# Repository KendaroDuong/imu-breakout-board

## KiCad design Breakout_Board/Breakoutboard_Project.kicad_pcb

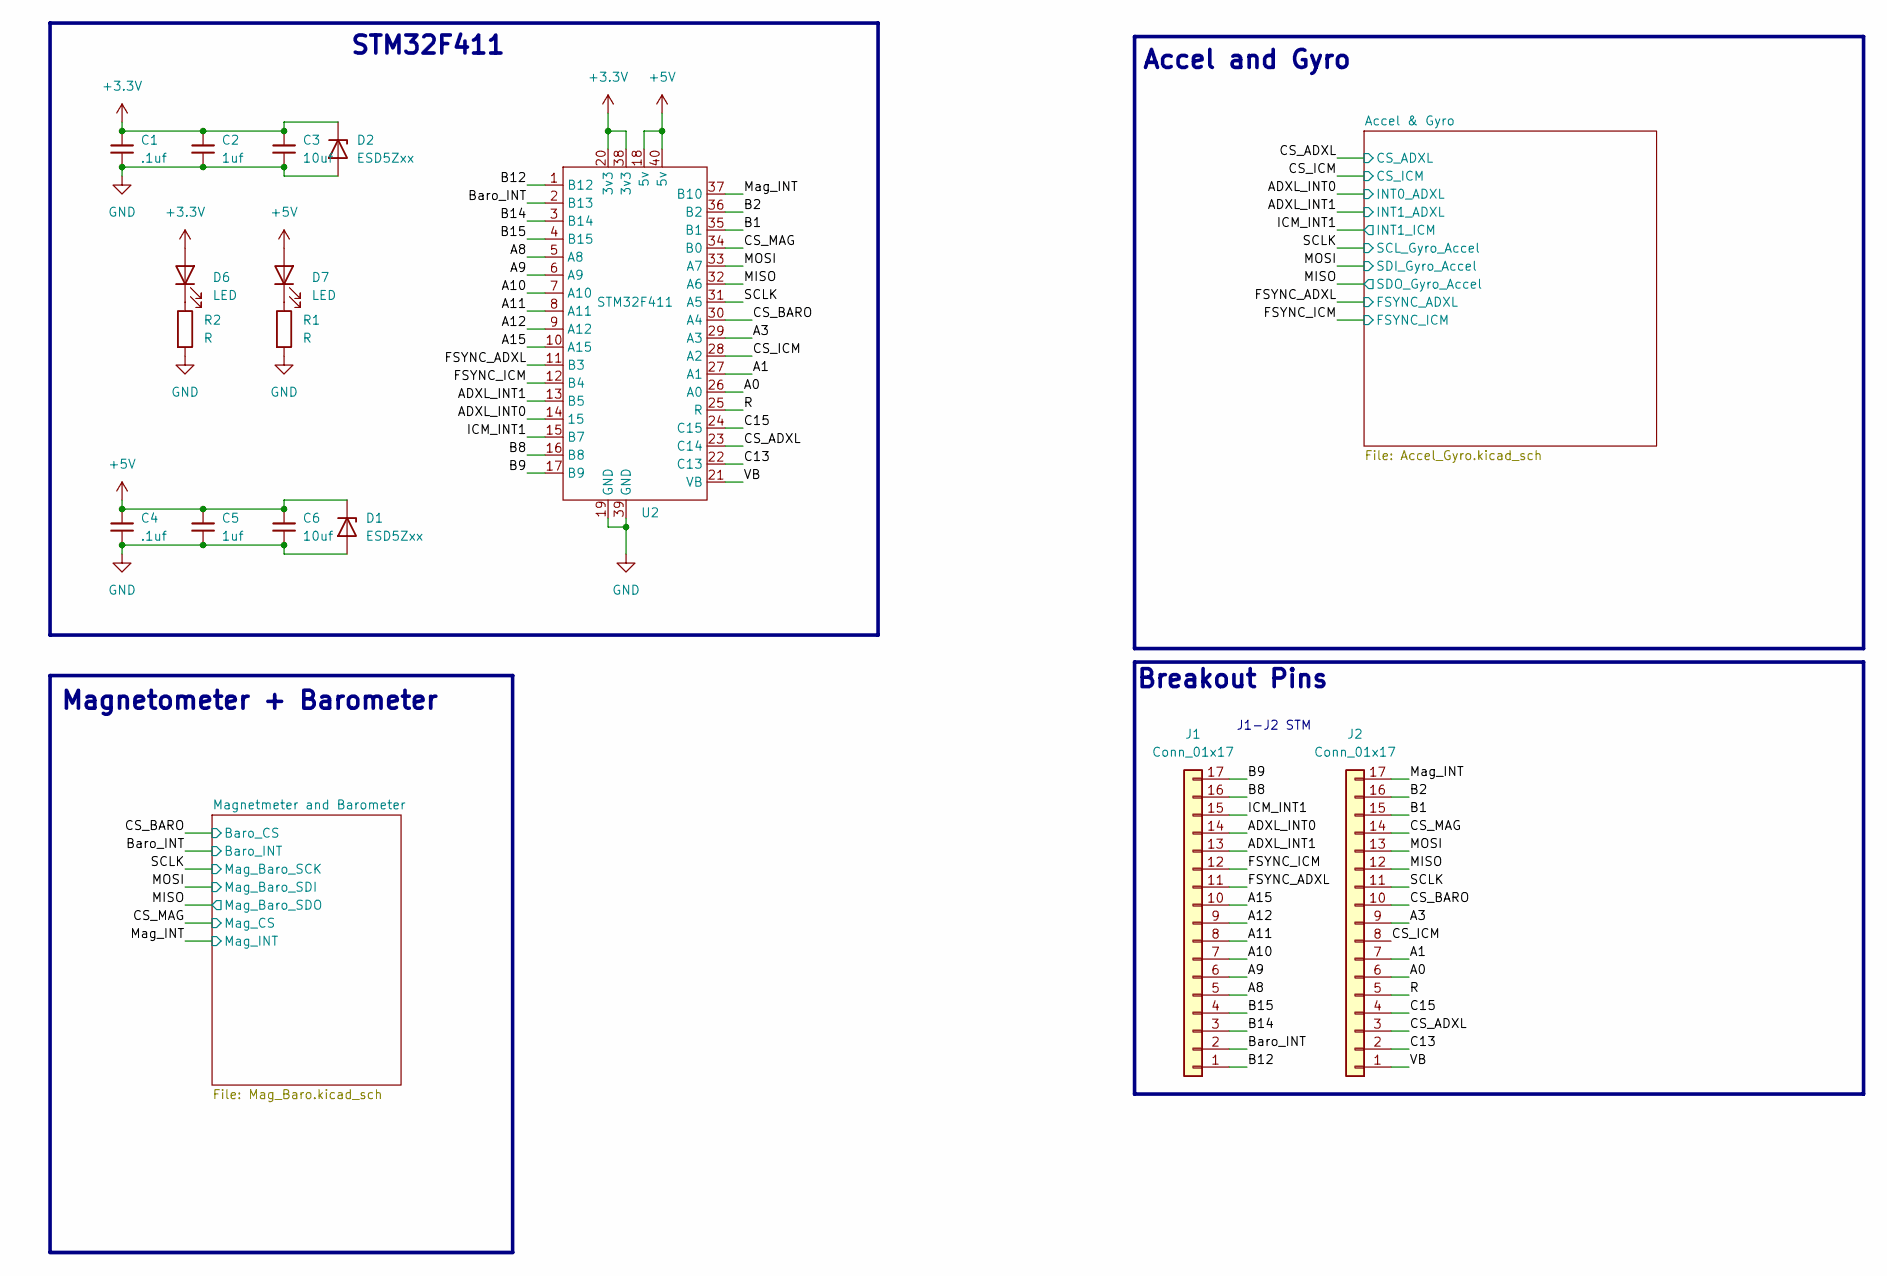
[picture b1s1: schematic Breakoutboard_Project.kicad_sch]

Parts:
C1, C4: .1uf; C_0805_2012Metric_Pad1.18x1.45mm_HandSolder
C2, C5: 1uf; C_0805_2012Metric_Pad1.18x1.45mm_HandSolder
C3, C6: 10uf; C_0805_2012Metric_Pad1.18x1.45mm_HandSolder
D1, D2: ESD5Zxx; D_SOD-523
D6, D7: LED; LED_0805_2012Metric_Pad1.15x1.40mm_HandSolder
J1, J2: Conn_01x17; PinHeader_1x17_P2.54mm_Vertical
R1, R2: R; LED_0805_2012Metric_Pad1.15x1.40mm_HandSolder
U2: STM32F411; BlackpillGeneric

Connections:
+3.3V: C1.1, C2.1, C3.1, D2.1 (K), D6.2 (A), U2.20 (3v3), U2.38 (3v3); also elsewhere on the board
+5V: C4.1, C5.1, C6.1, D1.1 (K), D7.2 (A), U2.18 (5v), U2.40 (5v)
/A0: J2.6, U2.26 (A0)
/A1: J2.7, U2.27 (A1)
/A3: J2.9, U2.29 (A3)
/A8: J1.5, U2.5 (A8)
/A9: J1.6, U2.6 (A9)
/A10: J1.7, U2.7 (A10)
/A11: J1.8, U2.8 (A11)
/A12: J1.9, U2.9 (A12)
/A15: J1.10, U2.10 (A15)
/ADXL_INT0: J1.14, U2.14 (15); also elsewhere on the board
/ADXL_INT1: J1.13, U2.13 (B5); also elsewhere on the board
/B1: J2.15, U2.35 (B1)
/B2: J2.16, U2.36 (B2)
/B8: J1.16, U2.16 (B8)
/B9: J1.17, U2.17 (B9)
/B12: J1.1, U2.1 (B12)
/B14: J1.3, U2.3 (B14)
/B15: J1.4, U2.4 (B15)
/Baro_INT: J1.2, U2.2 (B13); also elsewhere on the board
/C13: J2.2, U2.22 (C13)
/C15: J2.4, U2.24 (C15)
/CS_ADXL: J2.3, U2.23 (C14); also elsewhere on the board
/CS_BARO: J2.10, U2.30 (A4); also elsewhere on the board
/CS_ICM: J2.8, U2.28 (A2); also elsewhere on the board
/CS_MAG: J2.14, U2.34 (B0); also elsewhere on the board
/FSYNC_ADXL: J1.11, U2.11 (B3); also elsewhere on the board
/FSYNC_ICM: J1.12, U2.12 (B4); also elsewhere on the board
/ICM_INT1: J1.15, U2.15 (B7); also elsewhere on the board
/MISO: J2.12, U2.32 (A6); also elsewhere on the board
/MOSI: J2.13, U2.33 (A7); also elsewhere on the board
/Mag_INT: J2.17, U2.37 (B10); also elsewhere on the board
/R: J2.5, U2.25 (R)
/SCLK: J2.11, U2.31 (A5); also elsewhere on the board
/VB: J2.1, U2.21 (VB)
GND: C1.2, C2.2, C3.2, C4.2, C5.2, C6.2, D1.2 (A), D2.2 (A), R1.2, R2.2, U2.19 (GND), U2.39 (GND); also elsewhere on the board
unnamed: D6.1 (K), R2.1
unnamed: D7.1 (K), R1.1

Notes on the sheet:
Breakout Pins
STM32F411
Magnetometer + Barometer
Accel and Gyro
J1-J2 STM

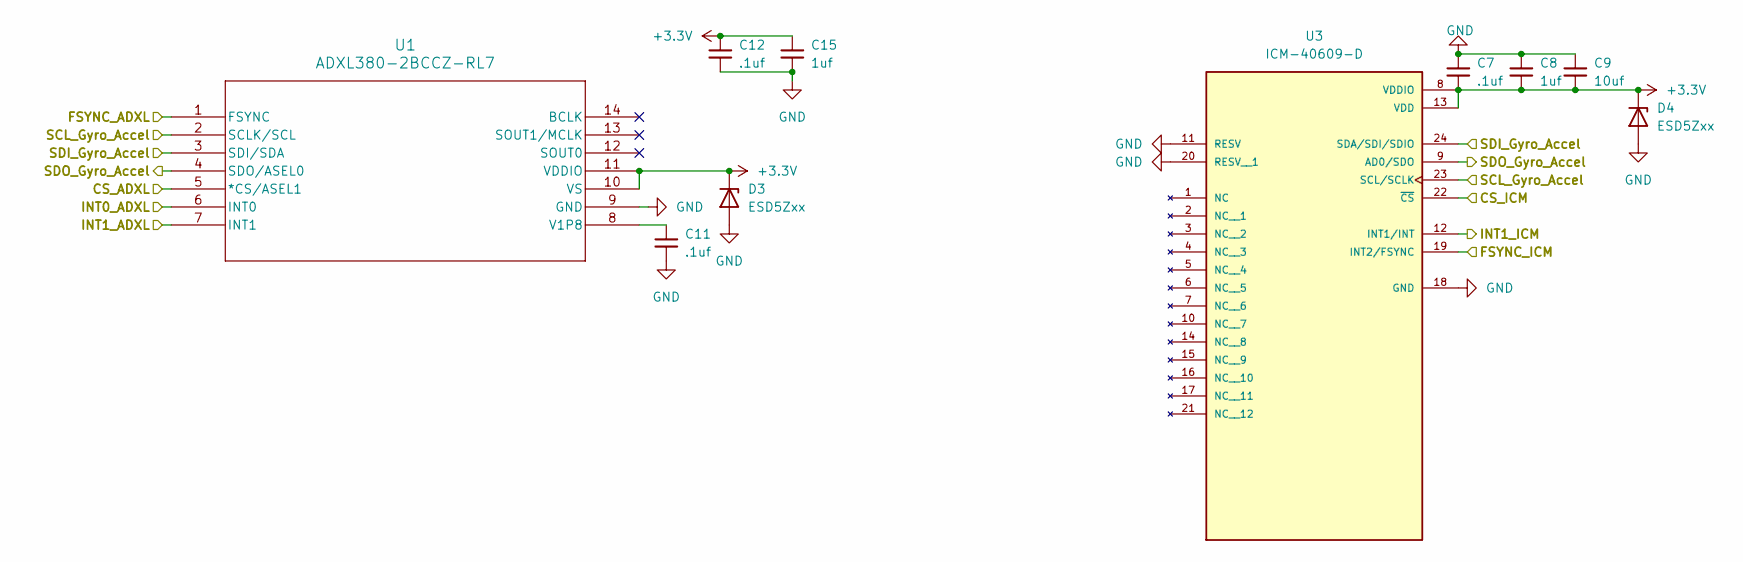
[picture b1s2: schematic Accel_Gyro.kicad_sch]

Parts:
C7, C11, C12: .1uf; C_0805_2012Metric_Pad1.18x1.45mm_HandSolder
C8, C15: 1uf; C_0805_2012Metric_Pad1.18x1.45mm_HandSolder
C9: 10uf; C_0805_2012Metric_Pad1.18x1.45mm_HandSolder
D3, D4: ESD5Zxx; D_SOD-523
U1: ADXL380-2BCCZ-RL7; CC-14-3_ADI
U3: ICM-40609-D; XDCR_ICM-40609-D; PARTREV 1.2

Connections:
+3.3V: C7.2, C8.2, C9.2, C12.1, C15.1, D3.1 (K), D4.1 (K), U1.10 (VS), U1.11 (VDDIO), U3.8 (VDDIO), U3.13 (VDD); also elsewhere on the board
/ADXL_INT0: U1.6 (INT0); also elsewhere on the board
/ADXL_INT1: U1.7 (INT1); also elsewhere on the board
/CS_ADXL: U1.5 (*CS/ASEL1); also elsewhere on the board
/CS_ICM: U3.22 (~CS); also elsewhere on the board
/FSYNC_ADXL: U1.1 (FSYNC); also elsewhere on the board
/FSYNC_ICM: U3.19 (INT2/FSYNC); also elsewhere on the board
/ICM_INT1: U3.12 (INT1/INT); also elsewhere on the board
/MISO: U1.4 (SDO/ASEL0), U3.9 (AD0/SDO); also elsewhere on the board
/MOSI: U1.3 (SDI/SDA), U3.24 (SDA/SDI/SDIO); also elsewhere on the board
/SCLK: U1.2 (SCLK/SCL), U3.23 (SCL/SCLK); also elsewhere on the board
GND: C7.1, C8.1, C9.1, C11.2, C12.2, C15.2, D3.2 (A), D4.2 (A), U1.9 (GND), U3.11 (RESV), U3.18 (GND), U3.20 (RESV__1); also elsewhere on the board
unnamed: C11.1, U1.8 (V1P8)

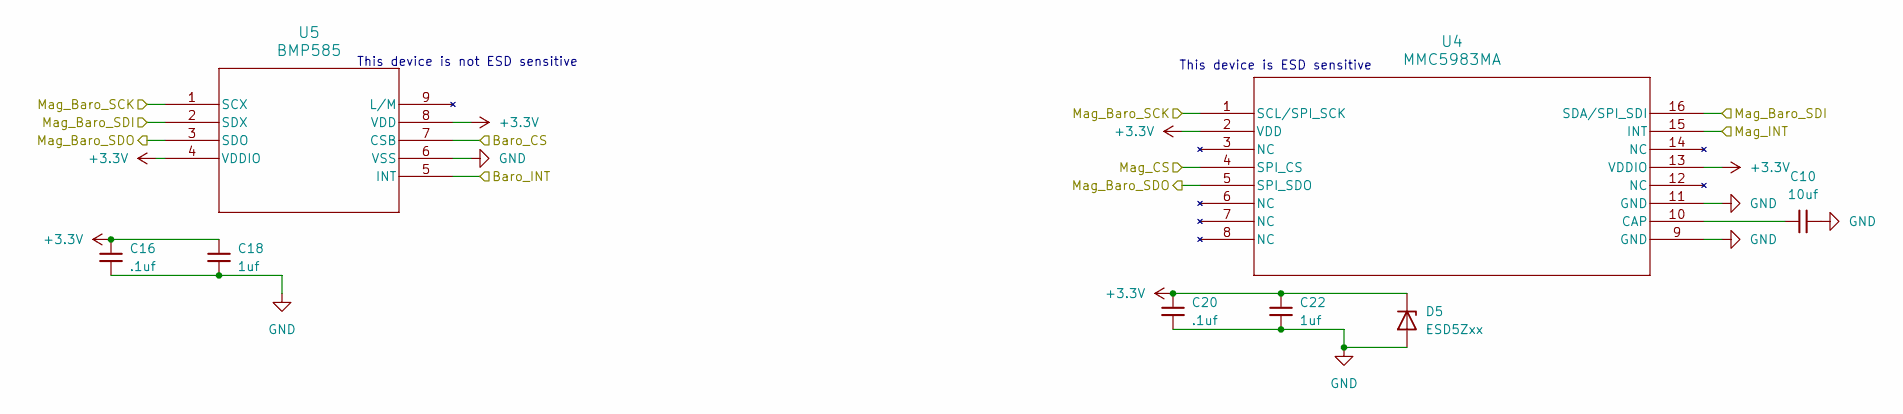
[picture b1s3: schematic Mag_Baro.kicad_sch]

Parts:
C10: 10uf; C_0805_2012Metric_Pad1.18x1.45mm_HandSolder
C16, C20: .1uf; C_0805_2012Metric_Pad1.18x1.45mm_HandSolder
C18, C22: 1uf; C_0805_2012Metric_Pad1.18x1.45mm_HandSolder
D5: ESD5Zxx; D_SOD-523
U4: MMC5983MA; MMC5983MA_MEM
U5: BMP585; LGA9_BMP585_BOS

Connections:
+3.3V: C16.1, C18.1, C20.1, C22.1, D5.1 (K), U4.2 (VDD), U4.13 (VDDIO), U5.4 (VDDIO), U5.8 (VDD); also elsewhere on the board
/Baro_INT: U5.5 (INT); also elsewhere on the board
/CS_BARO: U5.7 (CSB); also elsewhere on the board
/CS_MAG: U4.4 (SPI_CS); also elsewhere on the board
/MISO: U4.5 (SPI_SDO), U5.3 (SDO); also elsewhere on the board
/MOSI: U4.16 (SDA/SPI_SDI), U5.2 (SDX); also elsewhere on the board
/Mag_INT: U4.15 (INT); also elsewhere on the board
/SCLK: U4.1 (SCL/SPI_SCK), U5.1 (SCX); also elsewhere on the board
GND: C10.2, C16.2, C18.2, C20.2, C22.2, D5.2 (A), U4.9 (GND), U4.11 (GND), U5.6 (VSS); also elsewhere on the board
unnamed: C10.1, U4.10 (CAP)

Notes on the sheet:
This device is not ESD sensitive
This device is ESD sensitive

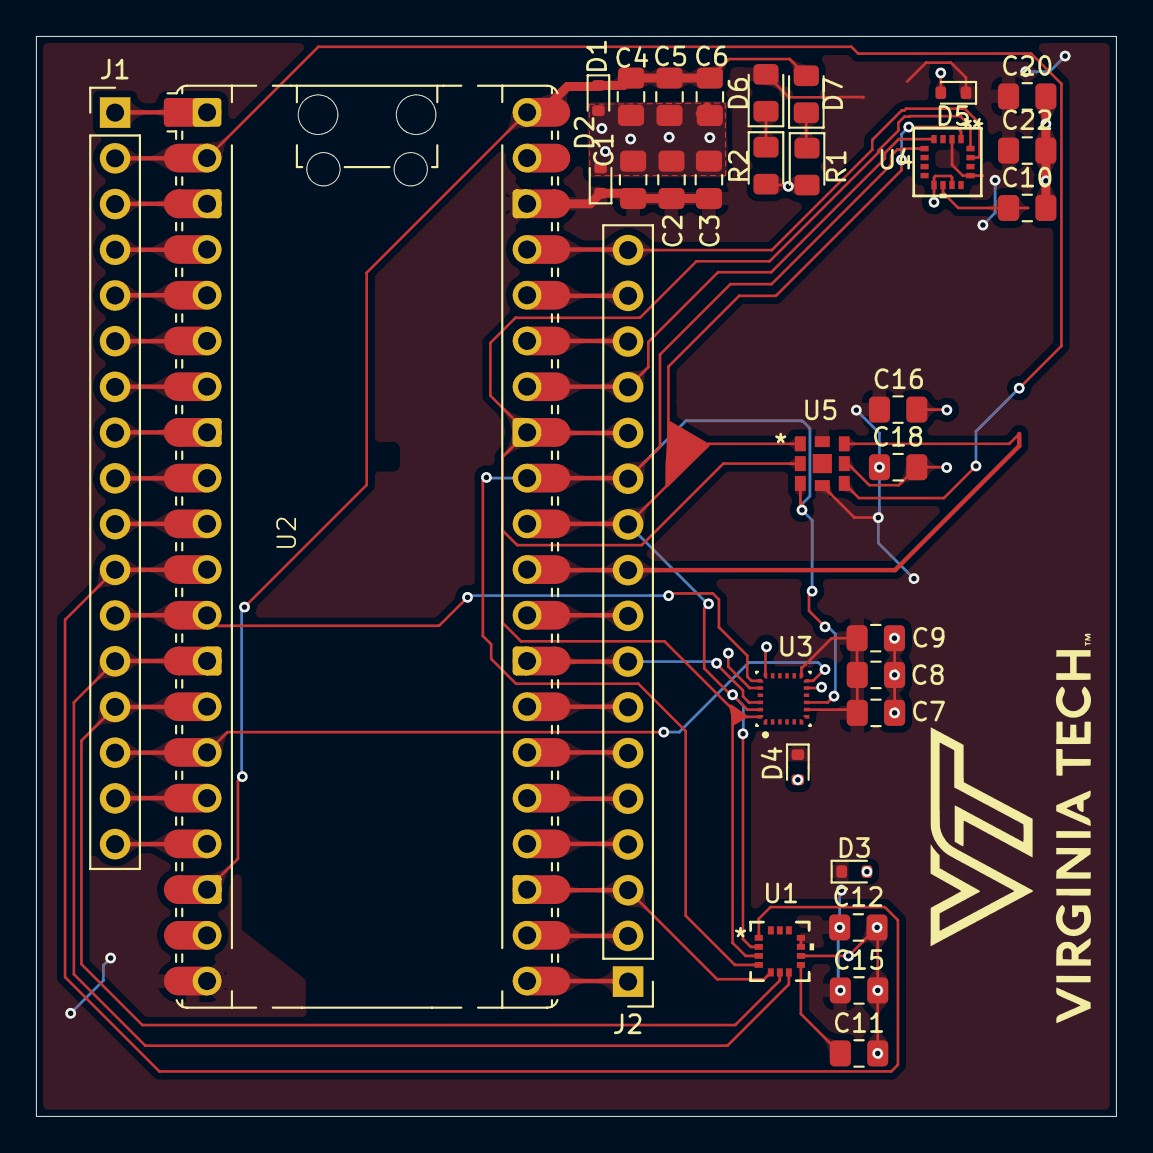
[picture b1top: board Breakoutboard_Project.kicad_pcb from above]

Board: 2 copper layers, 60.0 x 60.0 mm, 33 parts (0 on the bottom side), 41 nets.
